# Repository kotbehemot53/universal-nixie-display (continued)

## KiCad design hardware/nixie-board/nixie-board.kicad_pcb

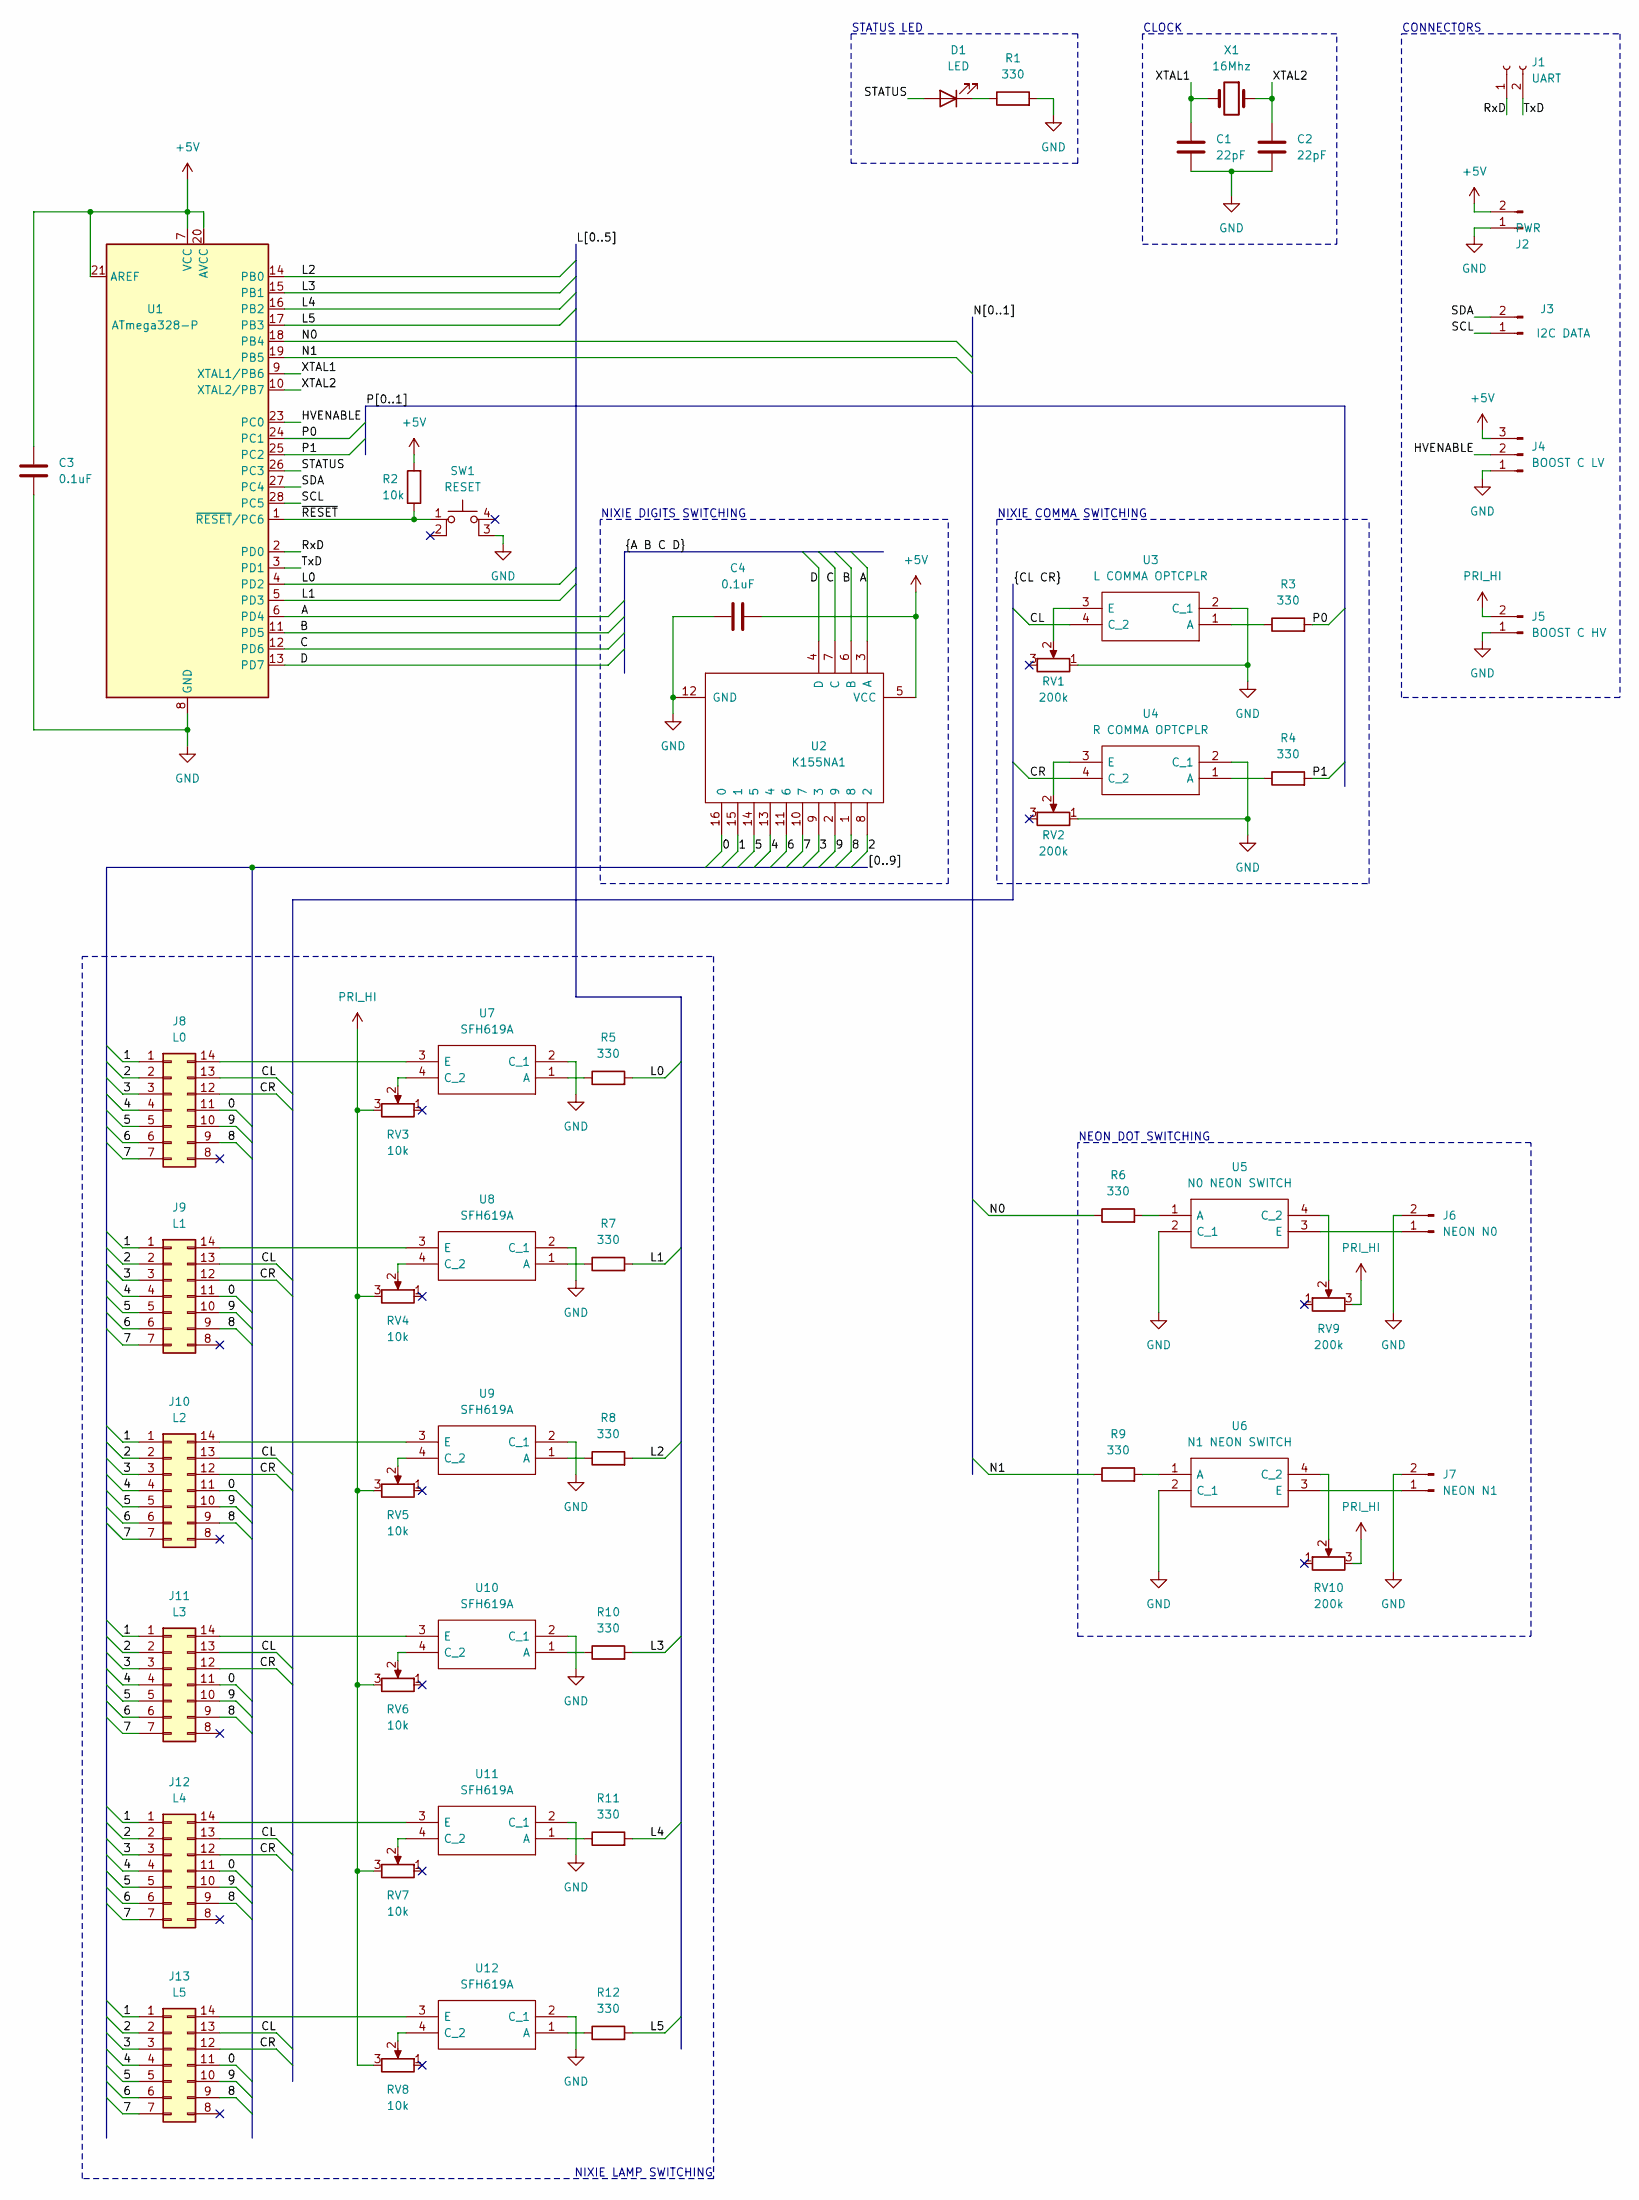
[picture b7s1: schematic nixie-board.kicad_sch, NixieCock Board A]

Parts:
C1, C2: 22pF; C_Disc_D3.0mm_W1.6mm_P2.50mm
C3, C4: 0.1uF; C_Disc_D5.0mm_W2.5mm_P2.50mm
D1: LED; LED_D3.0mm
J1: UART; PinHeader_1x02_P2.54mm_Vertical
J2: PWR; JST_XH_B2B-XH-A_1x02_P2.50mm_Vertical
J3: I2C DATA; JST_XH_B2B-XH-A_1x02_P2.50mm_Vertical
J4: BOOST C LV; JST_XH_B3B-XH-A_1x03_P2.50mm_Vertical
J5: BOOST C HV; JST_XH_B2B-XH-A_1x02_P2.50mm_Vertical
J6: NEON N0; JST_XH_B2B-XH-A_1x02_P2.50mm_Vertical
J7: NEON N1; JST_XH_B2B-XH-A_1x02_P2.50mm_Vertical
J8: L0; IDC-Header_2x07_P2.54mm_Vertical
J9: L1; IDC-Header_2x07_P2.54mm_Vertical
J10: L2; IDC-Header_2x07_P2.54mm_Vertical
J11: L3; IDC-Header_2x07_P2.54mm_Vertical
J12: L4; IDC-Header_2x07_P2.54mm_Vertical
J13: L5; IDC-Header_2x07_P2.54mm_Vertical
R1, R3, R4, R5, R6, R7, R8, R9, R10, R11, R12: 330; R_Axial_DIN0207_L6.3mm_D2.5mm_P10.16mm_Horizontal
R2: 10k; R_Axial_DIN0207_L6.3mm_D2.5mm_P10.16mm_Horizontal
RV1, RV2, RV9, RV10: 200k; Potentiometer_Bourns_3386F_Vertical
RV3, RV4, RV5, RV6, RV7, RV8: 10k; Potentiometer_Bourns_3386F_Vertical
SW1: RESET; SW_TH_Tactile_Omron_B3F-10xx
U1: ATmega328-P; DIP-28_W7.62mm
U2: K155NA1; DIP-16_W7.62mm
U3: L COMMA OPTCPLR; DIP762W56P254L469H470Q4N; Mouser Part Number 782-SFH619A
U4: R COMMA OPTCPLR; DIP762W56P254L469H470Q4N; Mouser Part Number 782-SFH619A
U5: N0 NEON SWITCH; DIP762W56P254L469H470Q4N; Mouser Part Number 782-SFH619A
U6: N1 NEON SWITCH; DIP762W56P254L469H470Q4N; Mouser Part Number 782-SFH619A
U7, U8, U9, U10, U11, U12: SFH619A; DIP762W56P254L469H470Q4N; Mouser Part Number 782-SFH619A
X1: 16Mhz; Crystal_HC49-4H_Vertical

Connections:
+5V: C3.1, C4.2, J2.2, J4.3, R2.2, U1.7 (VCC), U1.20 (AVCC), U1.21 (AREF), U2.5 (VCC)
/0: J8.11 (0), J9.11 (0), J10.11 (0), J11.11 (0), J12.11 (0), J13.11 (0), U2.16 (0)
/1: J8.1, J9.1, J10.1, J11.1, J12.1, J13.1, U2.15 (1)
/2: J8.2, J9.2, J10.2, J11.2, J12.2, J13.2, U2.8 (2)
/3: J8.3, J9.3, J10.3, J11.3, J12.3, J13.3, U2.9 (3)
/4: J8.4, J9.4, J10.4, J11.4, J12.4, J13.4, U2.13 (4)
/5: J8.5, J9.5, J10.5, J11.5, J12.5, J13.5, U2.14 (5)
/6: J8.6, J9.6, J10.6, J11.6, J12.6, J13.6, U2.11 (6)
/7: J8.7, J9.7, J10.7, J11.7, J12.7, J13.7, U2.10 (7)
/8: J8.9 (8), J9.9 (8), J10.9 (8), J11.9 (8), J12.9 (8), J13.9 (8), U2.1 (8)
/9: J8.10 (9), J9.10 (9), J10.10 (9), J11.10 (9), J12.10 (9), J13.10 (9), U2.2 (9)
/A: U1.6 (PD4), U2.3 (A)
/B: U1.11 (PD5), U2.6 (B)
/C: U1.12 (PD6), U2.7 (C)
/CL: J8.13 (CL), J9.13 (CL), J10.13 (CL), J11.13 (CL), J12.13 (CL), J13.13 (CL), U3.4 (C_2)
/CR: J8.12 (CR), J9.12 (CR), J10.12 (CR), J11.12 (CR), J12.12 (CR), J13.12 (CR), U4.4 (C_2)
/D: U1.13 (PD7), U2.4 (D)
/HVENABLE: J4.2, U1.23 (PC0)
/L0: R5.2, U1.4 (PD2)
/L1: R7.2, U1.5 (PD3)
/L2: R8.2, U1.14 (PB0)
/L3: R10.2, U1.15 (PB1)
/L4: R11.2, U1.16 (PB2)
/L5: R12.2, U1.17 (PB3)
/N0: R6.1, U1.18 (PB4)
/N1: R9.1, U1.19 (PB5)
/P0: R3.2, U1.24 (PC1)
/P1: R4.2, U1.25 (PC2)
/RxD: J1.1, U1.2 (PD0)
/SCL: J3.1, U1.28 (PC5)
/SDA: J3.2, U1.27 (PC4)
/STATUS: D1.2 (A), U1.26 (PC3)
/TxD: J1.2, U1.3 (PD1)
/XTAL1: C1.1, U1.9 (XTAL1/PB6), X1.2
/XTAL2: C2.1, U1.10 (XTAL2/PB7), X1.1
/~RESET: R2.1, SW1.1, U1.1 (~RESET/PC6)
GND: C1.2, C2.2, C3.2, C4.1, J2.1, J4.1, J5.1 (HV), J6.2, J7.2, R1.2, RV1.1, RV2.1, SW1.3 (K), U1.8 (GND), U1.22 (GND), U2.12 (GND), U3.2 (C_1), U4.2 (C_1), U5.2 (C_1), U6.2 (C_1), U7.2 (C_1), U8.2 (C_1), U9.2 (C_1), U10.2 (C_1), U11.2 (C_1), U12.2 (C_1)
unnamed: D1.1 (K), R1.1
unnamed: J6.1, U5.3 (E)
unnamed: J7.1, U6.3 (E)
unnamed: J8.14 (Anode), U7.3 (E)
unnamed: J9.14 (Anode), U8.3 (E)
unnamed: J10.14 (Anode), U9.3 (E)
unnamed: J11.14 (Anode), U10.3 (E)
unnamed: J12.14 (Anode), U11.3 (E)
unnamed: J13.14 (Anode), U12.3 (E)
unnamed: R3.1, U3.1 (A)
unnamed: R4.1, U4.1 (A)
unnamed: R5.1, U7.1 (A)
unnamed: R6.2, U5.1 (A)
unnamed: R7.1, U8.1 (A)
unnamed: R8.1, U9.1 (A)
unnamed: R9.2, U6.1 (A)
unnamed: R10.1, U10.1 (A)
unnamed: R11.1, U11.1 (A)
unnamed: R12.1, U12.1 (A)
unnamed: RV1.2, U3.3 (E)
unnamed: RV2.2, U4.3 (E)
unnamed: RV3.2, U7.4 (C_2)
unnamed: RV4.2, U8.4 (C_2)
unnamed: RV5.2, U9.4 (C_2)
unnamed: RV6.2, U10.4 (C_2)
unnamed: RV7.2, U11.4 (C_2)
unnamed: RV8.2, U12.4 (C_2)
unnamed: RV9.2, U5.4 (C_2)
unnamed: RV10.2, U6.4 (C_2)
PRI_HI: J5.2, RV3.3, RV4.3, RV5.3, RV6.3, RV7.3, RV8.3, RV9.3, RV10.3

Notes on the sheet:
NIXIE DIGITS SWITCHING
NIXIE LAMP SWITCHING
NEON DOT SWITCHING
NIXIE COMMA SWITCHING
STATUS LED
CONNECTORS
CLOCK

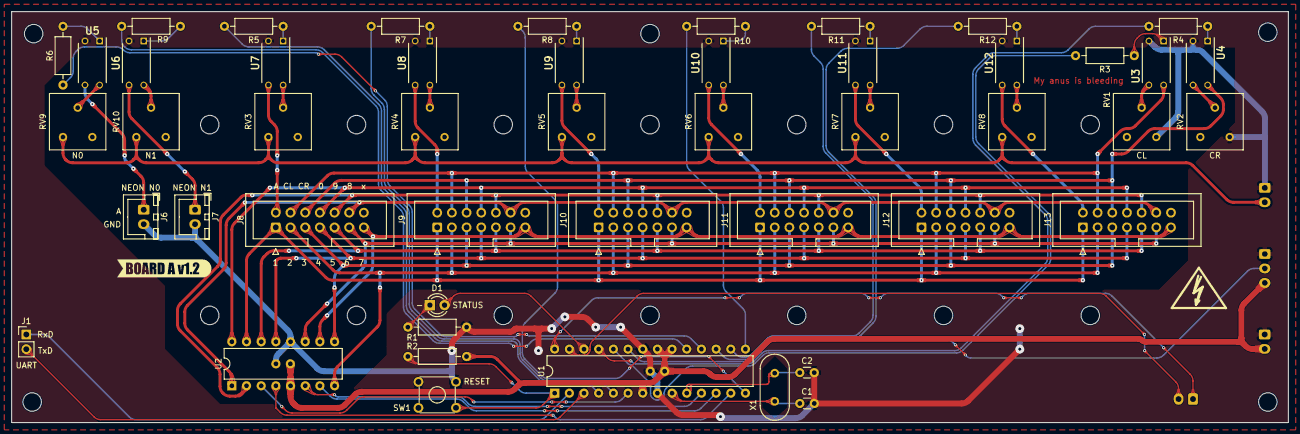
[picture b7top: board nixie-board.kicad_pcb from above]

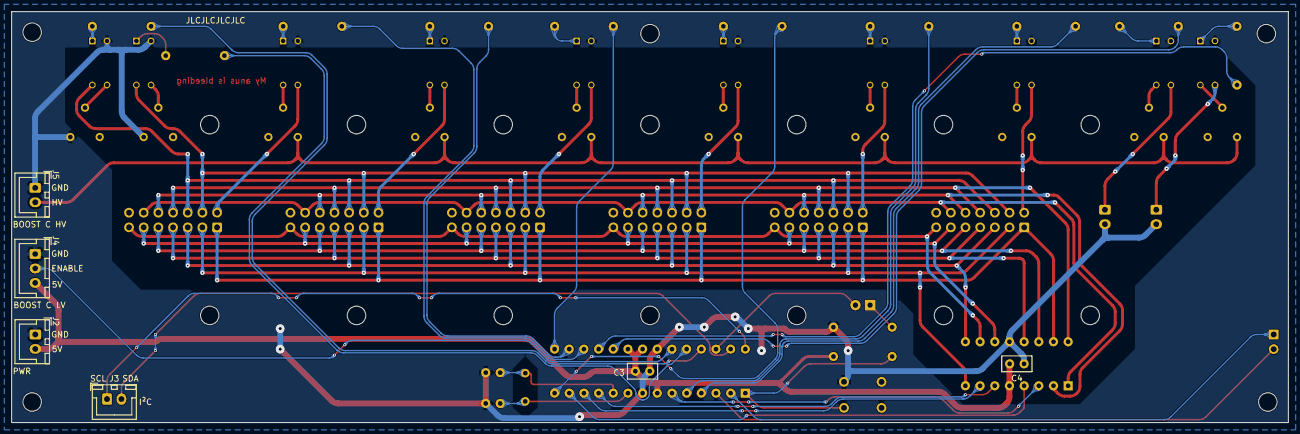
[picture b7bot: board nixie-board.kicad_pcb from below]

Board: 2 copper layers, 221.0 x 71.1 mm, 58 parts (6 on the bottom side), 67 nets.

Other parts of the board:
SYM_HV: Symbol_HighVoltage_Type2_CopperTop_VerySmall
kibuzzard-629EA4E7: G***; kibuzzard-629EA4E7
kibuzzard-6293E725: G***; kibuzzard-6293E725
kibuzzard-6293E830: G***; kibuzzard-6293E830

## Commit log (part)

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2021-04-10 init
2021-04-10 dimming experiment code copied
2021-04-10 function reorder
2021-04-10 xprmnt removed
2021-04-10 failed dimming idea removed
2021-04-10 todos
2021-04-10 todo
2021-04-10 typo
2021-04-11 say hello
2021-04-11 more sensible multiplexing
2021-04-18 display characters WIP
2021-04-18 binary dict + prep for letters
2021-04-18 displaying currentString
2021-04-18 debug + bezsmieciowosc
2021-04-21 all 8's for now
2021-04-21 vfd submodule
2021-04-21 nixie controller submodule
2021-04-21 I2C communication testing scripts for nixie
2021-04-21 raspberry added
2021-04-21 Create LICENSE
2021-04-21 minor improvements + todos
2022-07-17 TODO + hvenable + status + lamp points WIP
2022-07-17 delays include elapsed time
2022-07-17 2-6 digits support
2022-07-17 intro adapted to < 6 digits (when adding lamps left-right)
2022-07-17 digit ordering fixed
2022-07-17 points ordering adjustment
2022-07-17 debug for brightness depending on digits_used
2022-07-17 ON/OFF command + LR points commands WIP
2022-07-17 comment rmv
2022-07-17 lamp commas support
2022-07-17 commas in intro
2022-07-17 comments
2022-07-18 variable delays fixed
2022-07-18 cleanup
2022-07-18 new permanent intro + intro command
2022-08-21 todos, hvenable, commas,
2022-08-21 grid9 support, some fixes TODO wait after GRID9
2022-08-21 big dot/minus support, some cleanup
2023-01-23 custom bytes mode support
2023-01-24 redundant code removed + TODO
2023-01-24 an experiment in oorefac
2023-01-24 oo-refac WIP
2023-01-24 refac WIP
2023-01-24 on/off + whitespace
2023-01-25 removing animation from display WIP
2023-01-25 animator merging threads
2023-01-25 lil refac + proper frame length fix
2023-01-25 prepare enabling step changes between frames
2023-01-25 heartbeat multiframe animation
2023-01-25 grids animation revolution WIP
2023-01-25 passing thread steps + grid animation refac WIP
2023-01-25 nice n sexy grid 9 multiplexing
2023-01-25 old main removed
2023-01-25 a bit more renaming
2023-01-25 moar cleanup
2023-01-25 display init moved to constructor + cleanup
2023-01-26 setting display state WIP why big dot
2023-01-26 phantom big comma caused by bad idx type... fixed
2023-01-26 random bs
2023-01-26 unnecessary empty frame removed
2023-01-26 codeowners
2023-01-26 random WIP
2023-01-26 thread disabling working
2023-01-26 thread pointers instead of step array pointers
2023-01-27 generalized sinusoidal duty cycle gen + warning status led cycle
2023-01-27 animator failure listener
2023-01-27 led warning, more detailed text warning WIP TODO why actual 0??
2023-01-27 fail listener cleanup, animation retiming
2023-01-27 timing fix
2023-01-28 BS animation WIP
2023-01-28 silliness off for now
2023-01-28 prep proper lamp grid animation/dimming
2023-01-29 more groundwork for grid dimming
2023-01-29 digit fading WIP TODO does not quite work
2023-01-29 wtf, why the randomness!?
2023-01-29 help plz
2023-01-31 stupid indexing fixed
2023-01-31 sorry, now it's fixed
2023-01-31 fade out-in demo
2023-01-31 QOL improvements
2023-02-02 moar xprmnt
2023-02-03 fixed last digit animation - separate cooldown for digit9 switch
2023-02-03 rename GRID -> DIGIT where it makes sense
2023-02-03 nicer animation; sillier text; todo; micro fix
2023-02-03 test animation steps refac
2023-02-04 grid9 cooldown reduced after adding a pull-down resistor
2023-02-05 a mess
2023-02-05 a mess 2
2023-02-05 i2c commands buffering seems done
2023-02-05 minor refac, added command execution to animation
2023-02-05 commands prototype WIP
2023-02-10 missing include
2023-02-16 commands final form?
2023-02-16 lil fix
2023-03-04 debug off
2023-03-04 debug shit
2023-03-04 debug off, moar todos
2023-03-05 command execution WIP
2023-03-05 buncha debug, isOn
2023-03-05 intro sequencer + command
2023-03-06 remaining commands support WIP
2023-03-06 trash out
2023-03-06 buncha fixes
2023-03-06 CMD_CLEAR + INTRO_OFF update
2023-03-06 commands debug
2023-03-06 old comments out
2023-03-06 CLEAR bunchable; group commands; intro off doesn't set brightness
2023-03-06 group command debug
2023-03-06 buffers cleanup, impossible to reach out of buffer via commands
2023-03-06 lil cleanup
2023-03-06 moar debug just for fun
2023-03-06 readme update
2023-03-06 moar readme goodness
2023-03-06 a bit of a readme update
2023-03-06 readme
2023-03-06 master branches specified
2023-03-06 nixie controller module update
2023-03-06 vfd submodule update
2023-03-06 more functions, external interface support
2023-03-06 und-raspberry update
2023-03-07 main.cpp cleanup
2023-03-07 comments for display
2023-03-07 comments for IV18Animator
2023-03-07 some comments/doc
2023-03-07 DeviceAnimator constructor
2023-03-07 some comments, docs & renames
2023-03-07 some fixes + a new way to run animation step callback
2023-03-07 renames & comments
2023-03-07 neater debug
2023-03-07 some renames, led animation refac, square heartbeat
2023-03-07 commands to set led modes
2023-03-07 main.cpp cleaned up for production
2023-03-07 unnecessary directories removed
2023-03-12 raspberry boot/config files
2023-03-12 pi2VFD init
2023-03-12 who's the idiot
2023-03-12 lil refac + all vfd commands WIP
2023-03-12 sending current mode to vfd
2023-03-12 fixes
2023-03-12 minifix
2023-03-12 fix?
2023-03-12 idiotic error fix
2023-03-12 more idiocy fixed
2023-03-12 dimming vfd after some time after mode change WIP
2023-03-12 vfd dimming interval change
2023-03-13 xprmnt
2023-03-13 plep
2023-03-13 hm...
2023-03-13 temp fix
2023-04-09 power led
2023-04-09 poisoning prevention + whitespace
2023-04-09 poisoning prevention fix
2023-04-09 microfix
2023-04-09 random comment
2023-04-22 negative sleep fix
2023-04-22 option to select cputemp
2023-04-22 arg fix
2023-04-22 bugfix?
2023-04-22 randtest
2023-04-22 urlopen error handling
2023-04-23 gpu temp added
2023-04-23 CPU GPU mode
2023-04-23 nicer gpu str
2023-04-23 fix + comment
2023-04-24 different handling of http timeouts (no blinking 000000)
2023-04-24 intervals after i2c commands
2023-04-24 silly method name fixed
2023-04-24 unnecessary fix removed
2023-08-15 pausing i2c during buffer swap+read (doesn't help...)
2023-08-15 dashes - debug
2023-08-15 shorter buffers - don't do shit
2023-08-16 actual fix for the disappearing chars
2023-08-16 Revert "shorter buffers - don't do shit"
    This reverts commit 42a7f45efb020cc3794d6ae513d79ade58867866.
2023-08-17 letter "m" change
2023-08-17 board schematic
